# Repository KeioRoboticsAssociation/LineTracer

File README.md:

# ライントレーサーキット

## パーツリスト

|名前|個数|参考|
|:--|:--|:--|
|この基板|1|基板屋に受注してね|
|ターミナルブロック|4|[秋月電子](http://akizukidenshi.com/catalog/g/gP-02333/)|
|ピンソケット|15x1を2つ|[秋月電子](http://akizukidenshi.com/catalog/g/gC-05779/)|
|2SK4017(Q)|2|[秋月電子](http://akizukidenshi.com/catalog/g/gI-07597/)|
|TPR-105|2|[秋月電子](http://akizukidenshi.com/catalog/g/gI-03812/)|
|抵抗18kΩ|2|[秋月電子](http://akizukidenshi.com/catalog/g/gR-25183/)|
|抵抗240Ω|2|[秋月電子](http://akizukidenshi.com/catalog/g/gR-25241/)|
|TA4805SQ(パスコンセット)|1|[秋月電子](http://akizukidenshi.com/catalog/g/gI-00537/)|
|ギアボックス|1|[Amazon](https://www.amazon.co.jp/%E3%82%BF%E3%83%9F%E3%83%A4-%E6%A5%BD%E3%81%97%E3%81%84%E5%B7%A5%E4%BD%9C%E3%82%B7%E3%83%AA%E3%83%BC%E3%82%BA-No-168-%E3%83%80%E3%83%96%E3%83%AB%E3%82%AE%E3%83%A4%E3%83%9C%E3%83%83%E3%82%AF%E3%82%B9-%E5%B7%A6%E5%8F%B3%E7%8B%AC%E7%AB%8B4%E9%80%9F%E3%82%BF%E3%82%A4%E3%83%97/dp/B001Q13BIU)|
|電池ボックス|1|[秋月電子](http://akizukidenshi.com/catalog/g/gP-02671/)|
|Arduino nano|1|互換機をAliexpressなどで探す|
|ケーブル|適量||

## 作り方

instruction.pdfを読んでね。

## 基板の発注

gerber.zipを基板屋に投げるとラク。業者によっては拡張子の変更が必要かも。

## 写真

### 回路図

### 外観

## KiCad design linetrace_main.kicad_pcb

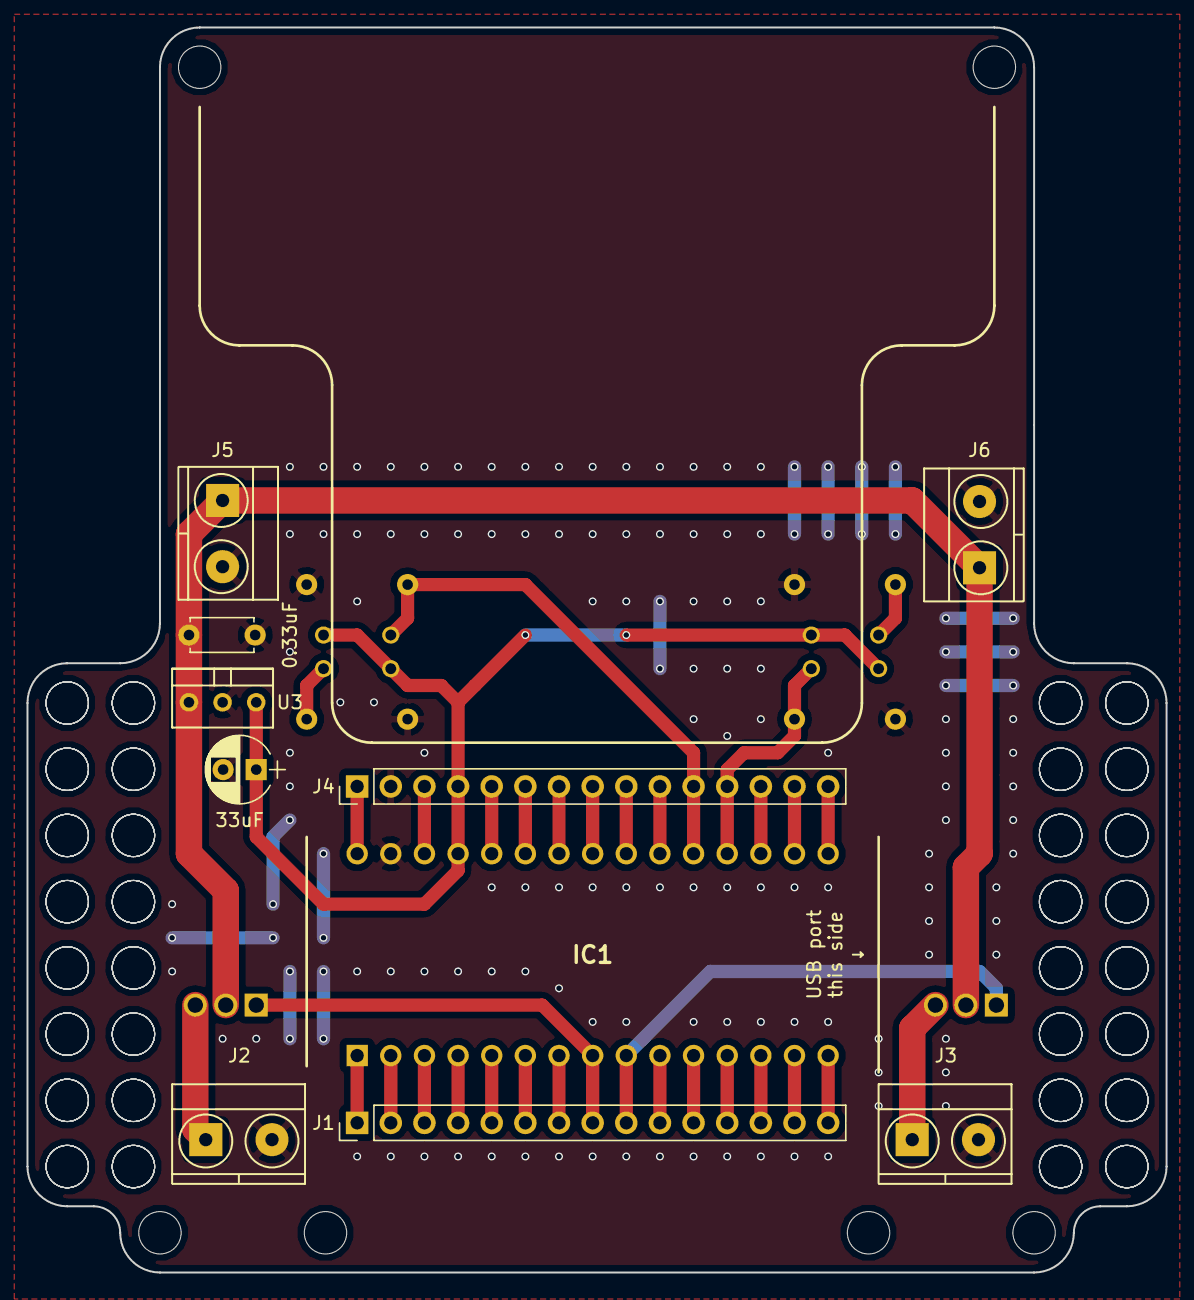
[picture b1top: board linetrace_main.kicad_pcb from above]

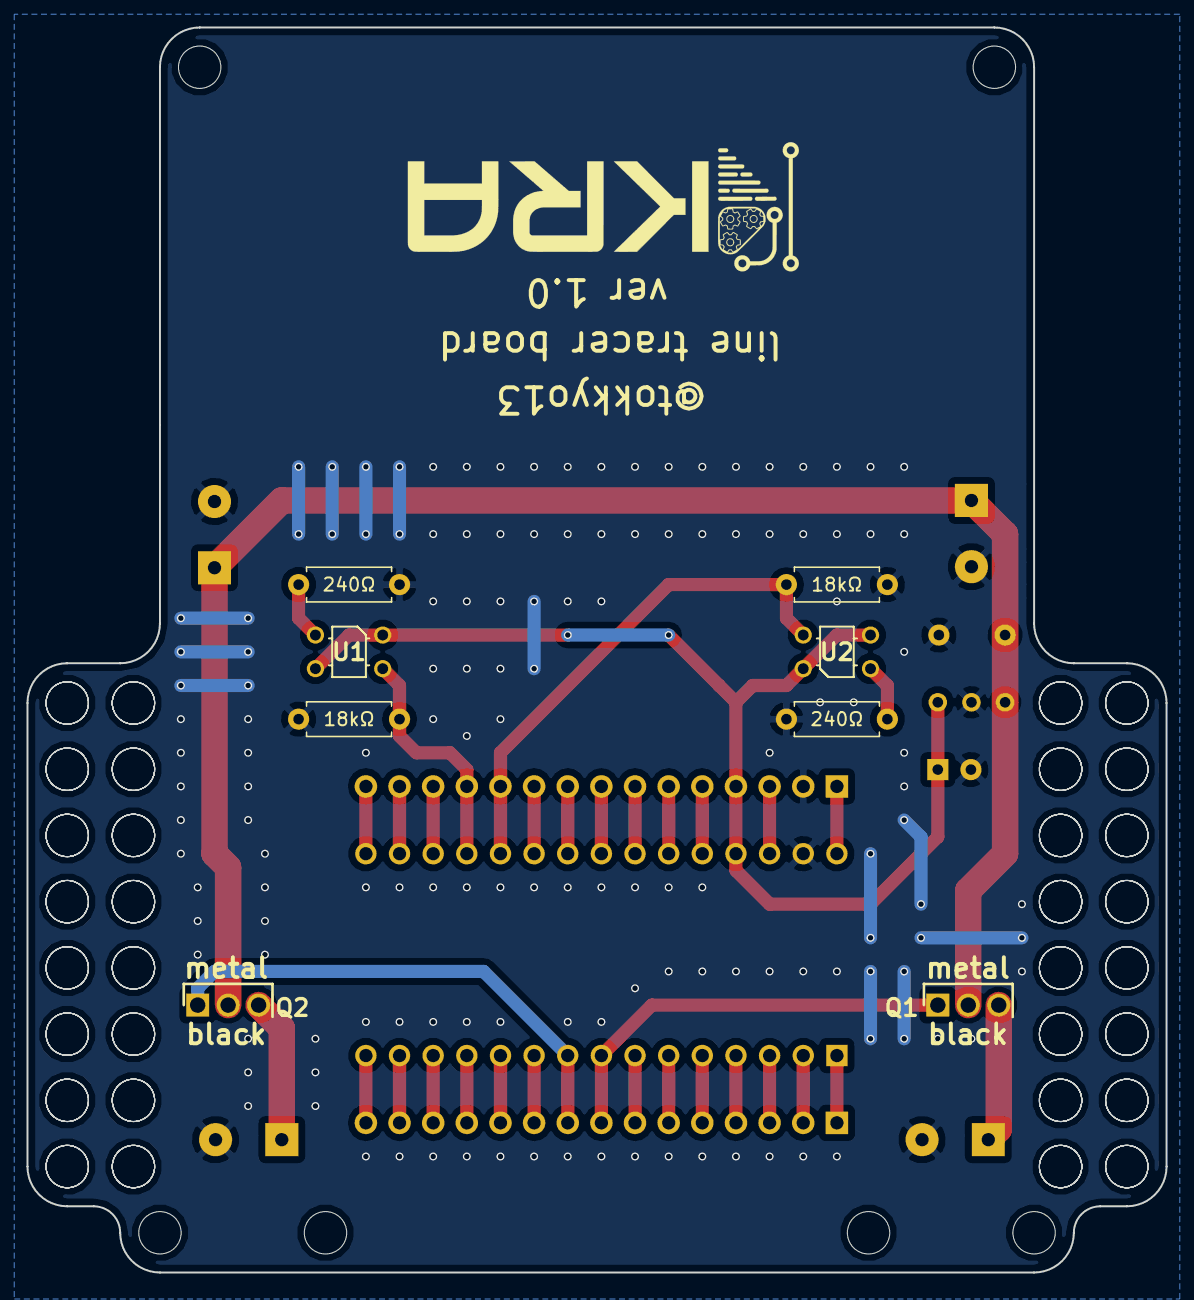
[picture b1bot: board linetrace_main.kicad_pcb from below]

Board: 2 copper layers, 86.0 x 94.0 mm, 18 parts (8 on the bottom side), 35 nets.

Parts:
0.33uF: 0.33uF; C_Disc_D4.7mm_W2.5mm_P5.00mm
18kΩ, 18kΩ#2: 18kΩ; R_Axial_DIN0207_L6.3mm_D2.5mm_P7.62mm_Horizontal
33uF: 33uF; CP_Radial_D5.0mm_P2.50mm
240Ω, 240Ω#2: 240Ω; R_Axial_DIN0207_L6.3mm_D2.5mm_P7.62mm_Horizontal
IC1: Nano; DIP1524W102P254L4318H762Q30N
J1, J4: Conn_01x15; Pin_Header_Straight_1x15_Pitch2.54mm
J2, J3, J5, J6: Conn_01x02; TerminalBlock_small
Q1, Q2: 2SK4017(Q); TO230P250X650X900-3P
U1, U2: TPR-105; TPR-105_new
U3: LD1117S12TR_SOT223; OldSowjetaera_Transistor_Type-I_SmallPads

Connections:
+5V: 33uF.1, IC1.27, J4.4, U1.1, U1.3, U2.1, U2.3, U3.2
+6V: 0.33uF.1, J5.1, J6.1, Q1.2, Q2.2, U3.3
/analog1: 18kΩ.2, IC1.19, J4.12, U1.4
/analog2: 18kΩ#2.2, IC1.20, J4.11, U2.4
/motor1: IC1.8, J1.8, Q1.1
/motor2: IC1.9, J1.9, Q2.1
GND: 0.33uF.2, 18kΩ.1, 18kΩ#2.1, 33uF.2, 240Ω.2, 240Ω#2.2, IC1.29, J2.2, J3.2, J4.2, J5.2, J6.2, U3.1
unnamed: IC1.1, J1.1
unnamed: IC1.2, J1.2
unnamed: IC1.3, J1.3
unnamed: IC1.4, J1.4
unnamed: IC1.5, J1.5
unnamed: IC1.6, J1.6
unnamed: IC1.7, J1.7
unnamed: IC1.10, J1.10
unnamed: IC1.11, J1.11
unnamed: IC1.12, J1.12
unnamed: IC1.13, J1.13
unnamed: IC1.14, J1.14
unnamed: IC1.15, J1.15
unnamed: IC1.16, J4.15
unnamed: IC1.17, J4.14
unnamed: IC1.18, J4.13
unnamed: IC1.21, J4.10
unnamed: IC1.22, J4.9
unnamed: IC1.23, J4.8
unnamed: IC1.24, J4.7
unnamed: IC1.25, J4.6
unnamed: IC1.26, J4.5
unnamed: IC1.28, J4.3
unnamed: IC1.30, J4.1
unnamed: J2.1, Q1.3
unnamed: J3.1, Q2.3
unnamed: 240Ω.1, U1.2
unnamed: 240Ω#2.1, U2.2

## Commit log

2018-10-25 edited readme.md
2018-10-26 removed fucking .DS_Store
